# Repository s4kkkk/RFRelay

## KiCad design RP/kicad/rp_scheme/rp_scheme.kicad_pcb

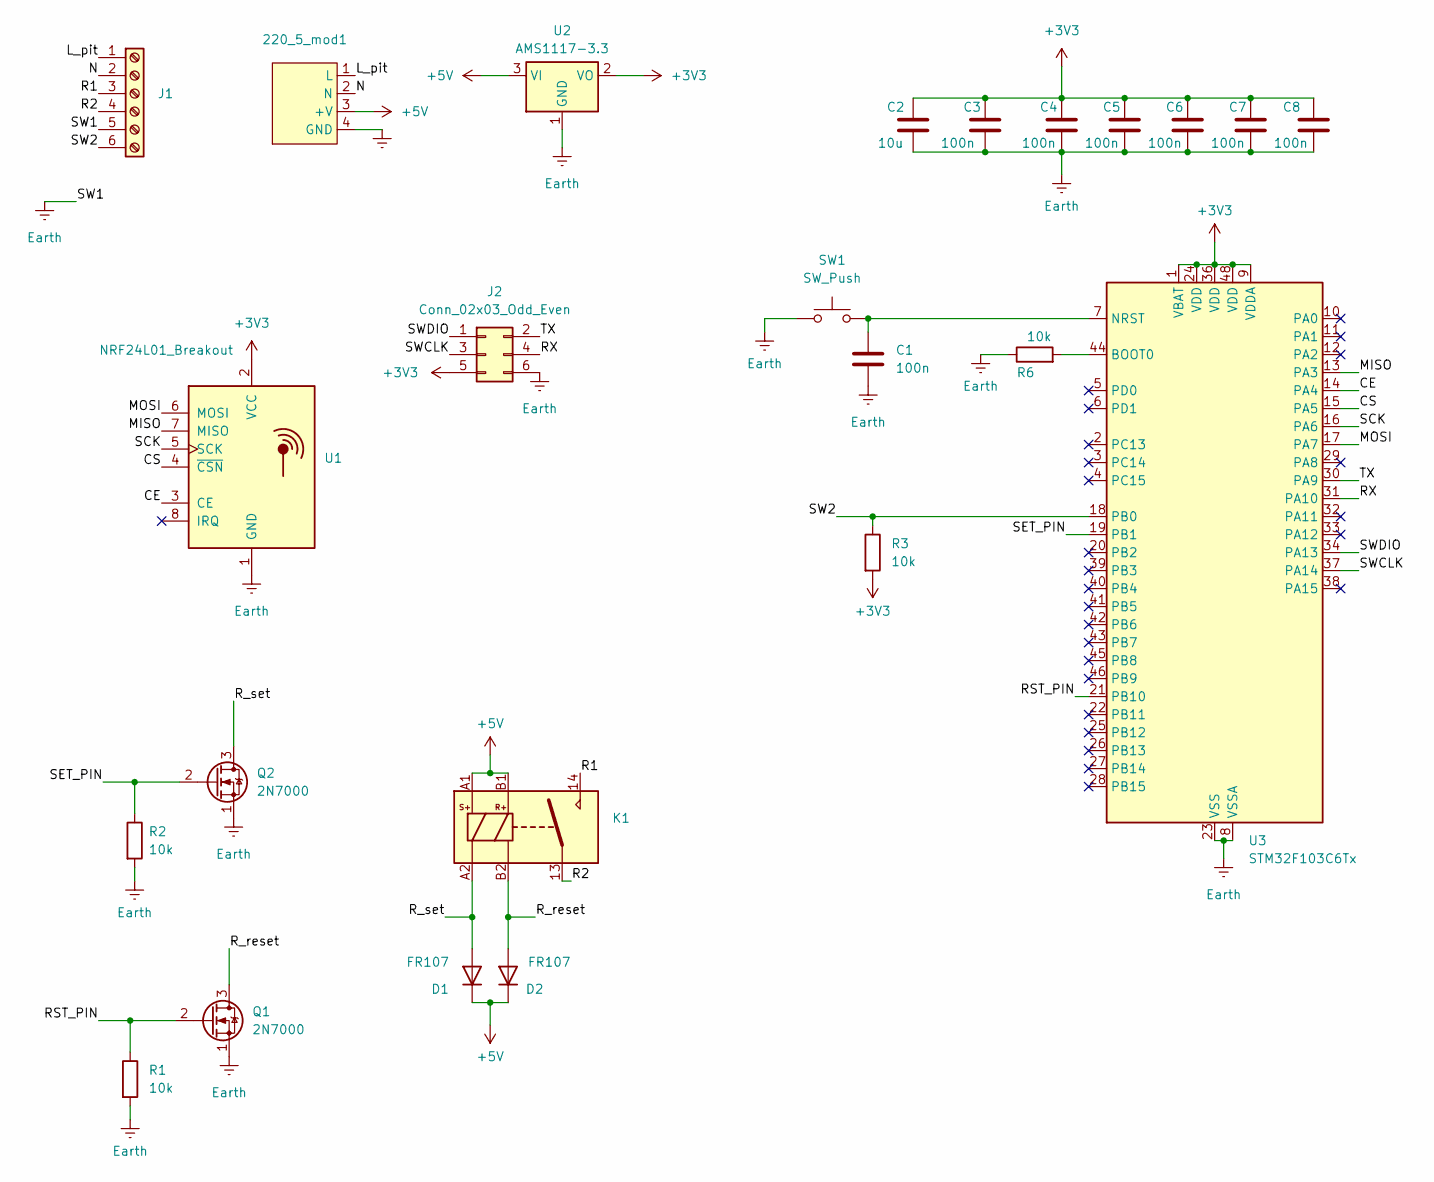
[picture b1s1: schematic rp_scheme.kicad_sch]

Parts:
220_5_mod1: 220_5_mod
C1, C3, C4, C5, C6, C7, C8: 100n; C_0603_1608Metric
C2: 10u; C_0603_1608Metric
D1, D2: FR107; D_DO-34_SOD68_P7.62mm_Horizontal
J1: Screw_Terminal_01x06; TerminalBlock_MaiXu_MX126-5.0-06P_1x06_P5.00mm
J2: Conn_02x03_Odd_Even; PinHeader_2x03_P2.54mm_Vertical
K1: Relay_SPST_Latching_2coil; Relay
Q1, Q2: 2N7000; TO-92_Inline
R1, R2, R3, R6: 10k; R_0603_1608Metric
SW1: SW_Push; SW_PUSH_6mm_H4.3mm
U1: NRF24L01_Breakout; NRF24L01-SMD
U2: AMS1117-3.3; SOT-223-3_TabPin2
U3: STM32F103C6Tx; LQFP-48_7x7mm_P0.5mm

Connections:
+3V3: C2.1, C3.1, C4.1, C5.1, C6.1, C7.1, C8.1, J2.5, R3.2, U1.2 (VCC), U2.2 (VO), U3.1 (VBAT), U3.9 (VDDA), U3.24 (VDD), U3.36 (VDD), U3.48 (VDD)
+5V: 220_5_mod1.3 (+V), D1.1 (K), D2.1 (K), K1.A1, K1.B1, U2.3 (VI)
/CE: U1.3 (CE), U3.14 (PA4)
/CS: U1.4 (~CSN), U3.15 (PA5)
/L_pit: 220_5_mod1.1 (L), J1.1
/MISO: U1.7 (MISO), U3.13 (PA3)
/MOSI: U1.6 (MOSI), U3.17 (PA7)
/N: 220_5_mod1.2 (N), J1.2
/R1: J1.3, K1.14
/R2: J1.4, K1.13
/RST_PIN: Q1.2 (G), R1.1, U3.21 (PB10)
/RX: J2.4, U3.31 (PA10)
/R_reset: D2.2 (A), K1.B2, Q1.3 (D)
/R_set: D1.2 (A), K1.A2, Q2.3 (D)
/SCK: U1.5 (SCK), U3.16 (PA6)
/SET_PIN: Q2.2 (G), R2.1, U3.19 (PB1)
/SW2: J1.6, R3.1, U3.18 (PB0)
/SWCLK: J2.3, U3.37 (PA14)
/SWDIO: J2.1, U3.34 (PA13)
/TX: J2.2, U3.30 (PA9)
Earth: 220_5_mod1.4 (GND), C1.2, C2.2, C3.2, C4.2, C5.2, C6.2, C7.2, C8.2, J1.5, J2.6, Q1.1 (S), Q2.1 (S), R1.2, R2.2, R6.1, SW1.1, U1.1 (GND), U2.1 (GND), U3.8 (VSSA), U3.23 (VSS), U3.35 (VSS), U3.47 (VSS)
unnamed: R6.2, U3.44 (BOOT0)
unnamed: C1.1, SW1.2, U3.7 (NRST)

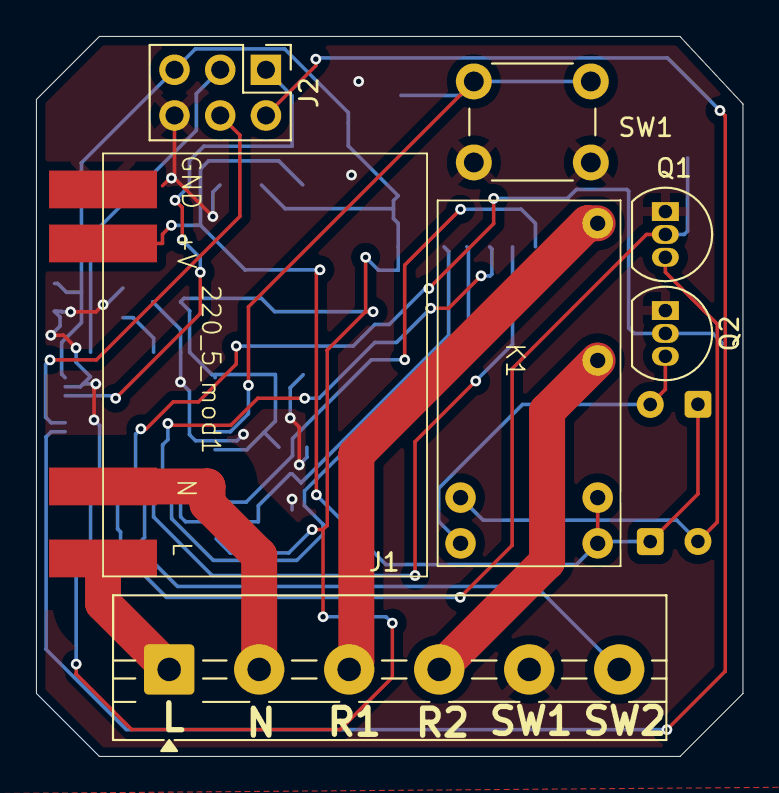
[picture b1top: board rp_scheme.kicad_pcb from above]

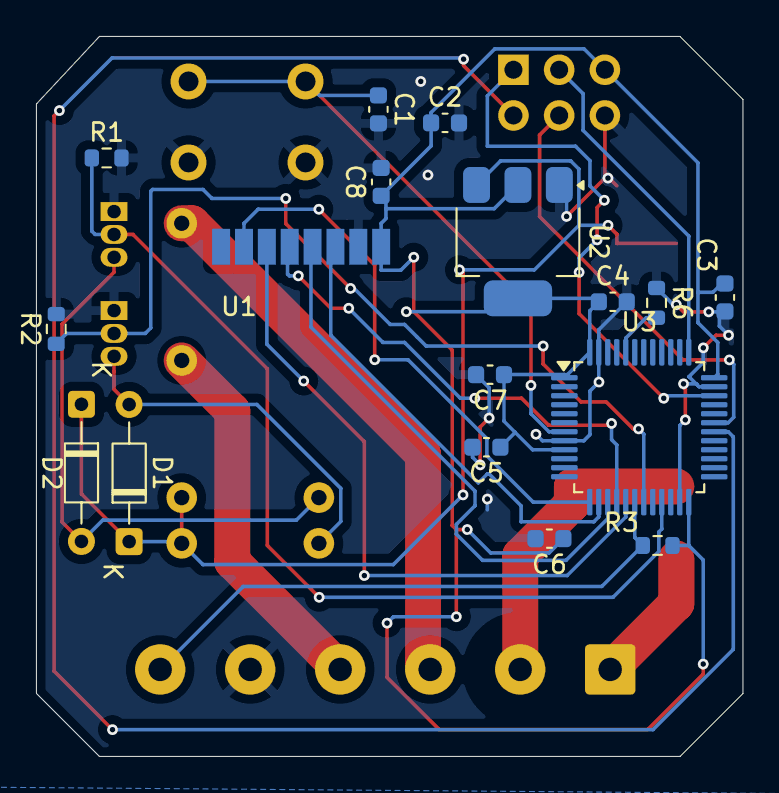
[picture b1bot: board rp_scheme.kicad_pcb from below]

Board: 2 copper layers, 39.2 x 40.0 mm, 24 parts (17 on the bottom side), 23 nets.

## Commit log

2025-02-07 Определена начальная структура проекта
2025-02-09 Добавлена подсистема device
2025-02-10 gpio: добавлен хедер, определено driver-api
2025-02-10 незначительные изменения
2025-02-10 gpio: подсистема реализована
2025-02-13 gpio драйвер для stm32: добавил хедер с описанием интерфейса
2025-02-14 GPIO-драйвер stm32: добавил реализацию основных функций
2025-02-15 Добавил низкоуровневую инициализацию; Исправил ошибки с квалификатороми
2025-02-16 Изменена логика сборки
2025-02-17 main/: изменена логика инициализации проекта
2025-02-18 uart_api: Добавлено объявление API-подсистемы
2025-02-19 uart: добавлены файлы с реализацией
2025-02-19 uart: начата реализация uart-драйвера
2025-02-20 uart: реализована функция передатчика
2025-02-21 изменена структура каталогов
2025-02-21 uart: добавлена реализация автомата, выполняющего прием. Изменен uart-api.
2025-02-23 uart: драйвер реализован
2025-02-24 добавлена функция printk с форматным выводом; добавлены каталоги с примерами
2025-02-27 незначительные изменения структуры проекта
2025-03-01 nrf24l01: определен интерфейс к драйверам. Начал реализовывать soft-драйвер (за основу взят https://github.com/kehribar/nrf24L01_plus )
2025-03-01 nrf24l01: драйвер nrf24l01 реализован
2025-03-03 nrf24l01_soft_driver: добавлен пример кода передатчика
2025-03-05 samples: добавлен код приемника
2025-05-11 Добавлены каталоги для УУ и РП
2025-05-12 Добавлено определение стурктуры пакетов данных
2025-05-12 UU: инициализация всех подсистем
2025-05-12 удален мусор doxygen
2025-05-13 U: вся конфигурация вынесена в config.h
2025-06-01 добавлены: работа с SysTick, на ее основе добавлены пользовательские таймеры
2025-06-01 УУ: начал реализовывать КА; nrf24l01: добавлен метод для получения текущего активного канала
2025-06-01 УУ: КА завершен
2025-06-02 РП: в каталог прошивки добавлены: код таймеров + код SysTick
2025-06-02 РП: перенесены основные файлы из УУ в каталог для РП
2025-06-02 РП: реализован КА, поддерживающий соединение
2025-06-03 РП: реализован КА.
2025-06-03 РП: удален .clangd
2025-06-03 РП: незначительные изменения
2025-06-03 РП: незначительные изменения. Исправлены некоторые баги
2025-06-03 УУ: изменены TX и RX MAC-адреса. Изменено определение макроса DEBUG()
2025-06-03 Удален .clangd
2025-06-03 УУ: незначительные изменения. Исправлены некоторые баги
2025-06-03 УУ: функция рабочего такта КА добавлена в суперцикл. Расширена система логирования
2025-06-03 Изменено название функции для проверки контрольной суммы
2025-06-04 УУ: Исправлен критический баг в коде драйвера nrf24l01. Первая рабочая версия проекта
2025-06-04 РП: Исправлен критический баг в коде драйвера nrf24l01. Первая рабочая версия проекта
2025-06-05 УУ: изменена конфигурация
2025-06-05 РП: Добавлена возможность отправки нескольких пакетов для ответа на beacon. Повышена стабильность поиска частоты.
2025-06-11 РП: корректировка работы с реле. Добавлена логика работы с двумя контактами реле: SET и RST
2025-06-11 РП: добавлен автомат для управления индикацией
2025-06-11 РП: исправлен баг с конфигурацией старших битов GPIO-регистров в драйвере
2025-06-12 УУ: исправлен баг с конфигурацией старших битов GPIO-регистров в драйвере
2025-06-12 УУ: добавлена индикация
2025-06-13 УУ: незначительные изменения
2025-06-19 УУ: добавлена схема kicad
2025-06-19 УУ: незначательные изменения
2025-06-19 РП: добавлена схема
2025-06-20 РП: разводка платы завершен
2025-06-21 РП: изменены габариты платы
